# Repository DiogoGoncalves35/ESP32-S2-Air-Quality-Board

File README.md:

# ESP32-S2 Air Quality Board

An IoT Air Quality Monitor

This board is designed to measure TVOC (Total Volatile Organic Compounds), eCO2(Estimated Concentration of Carbon Dioxide) and calculate AQI (Air Quality Index) of the ambient arround. 

It's a very simple design, it was designed with the intetion of testing ENS160 + AHT21 module. 
In the end AHT21 sensor is not used because ENS160 has a heater and influences temperature readings, values are about 5 degrees higher then they shoud be.

At the moment the LVGL interface only shows eCO2 and AQI values, there is no information about TVOC, Wi-Fi and MQTT status.

------------

### Home Assistant

It supports Home Assistant via HA MQTT Auto Discovery,  there is no need to integrate this device via web interface or yaml code, it's a faster solution to integrate devices. 
The microcontroller sends TVOC, eCO2 and AQI values, and also a "On" message. Values are send every 15 seconds and if there is no value recevied 35 seconds after the last, HA assumes that the device is offline.

------------

### Schematic

The [schematic](/PCB/Schematic.pdf) is designed arround ESP32-S2 Mini Board, LCD connects via SPI and ENS160 with I²C. Board can be powered with 5V from USB connector or via ESP32-S2 Mini Board USB connector. The AJ38 module step downs the voltage to 3.3V, and powers the components. A buzzer was added but at the moment is not in use.

------------

### PCB

[This PCB](/PCB) has a very simple design, it's a 1.6 mm board with 2 copper layers, both connect to GND. Next version should have a better design, the microcontroller must be at one edge, or the GND pour needs to be removed under, it's a good practice when there is an antenna.

------------

### Code

Every line of [code](/Code/Air%20Quality%20Monitor) contains a commentary. Some libraries need a few changes.

Configuration for User_Setup.h (TFT_eSPI Library)
```arduino
#define ST7735_DRIVER

#define TFT_RGB_ORDER TFT_RGB
#define TFT_WIDTH  160
#define TFT_HEIGHT 128

#define TFT_MOSI  35
#define TFT_SCLK  36
#define TFT_CS    34  
#define TFT_DC    33  
#define TFT_RST   18
```

Configuration for lv_conf.h (lvgl Library)
```arduino
#if 1

#define LV_TICK_CUSTOM 1

#define LV_FONT_MONTSERRAT_10 1
#define LV_FONT_MONTSERRAT_12 1
#define LV_FONT_MONTSERRAT_14 1

```

------------

### Known issues

- No I²C Pull-Up (Sometimes module is not detected)
- ESP32-S2 need serial in other to work (Without module not works)
- Mounting Holes connected to GND

------------

### To-Do

- Better hardware design
- Other sensor to compare
- ESP32-S3 WROOM (No more boards)
- New LVGL interface
- Add restart button via Home Assistant
- USB-C
- Maybe LCD without the module
- Control LCD led backlight with a mosfet/transistor

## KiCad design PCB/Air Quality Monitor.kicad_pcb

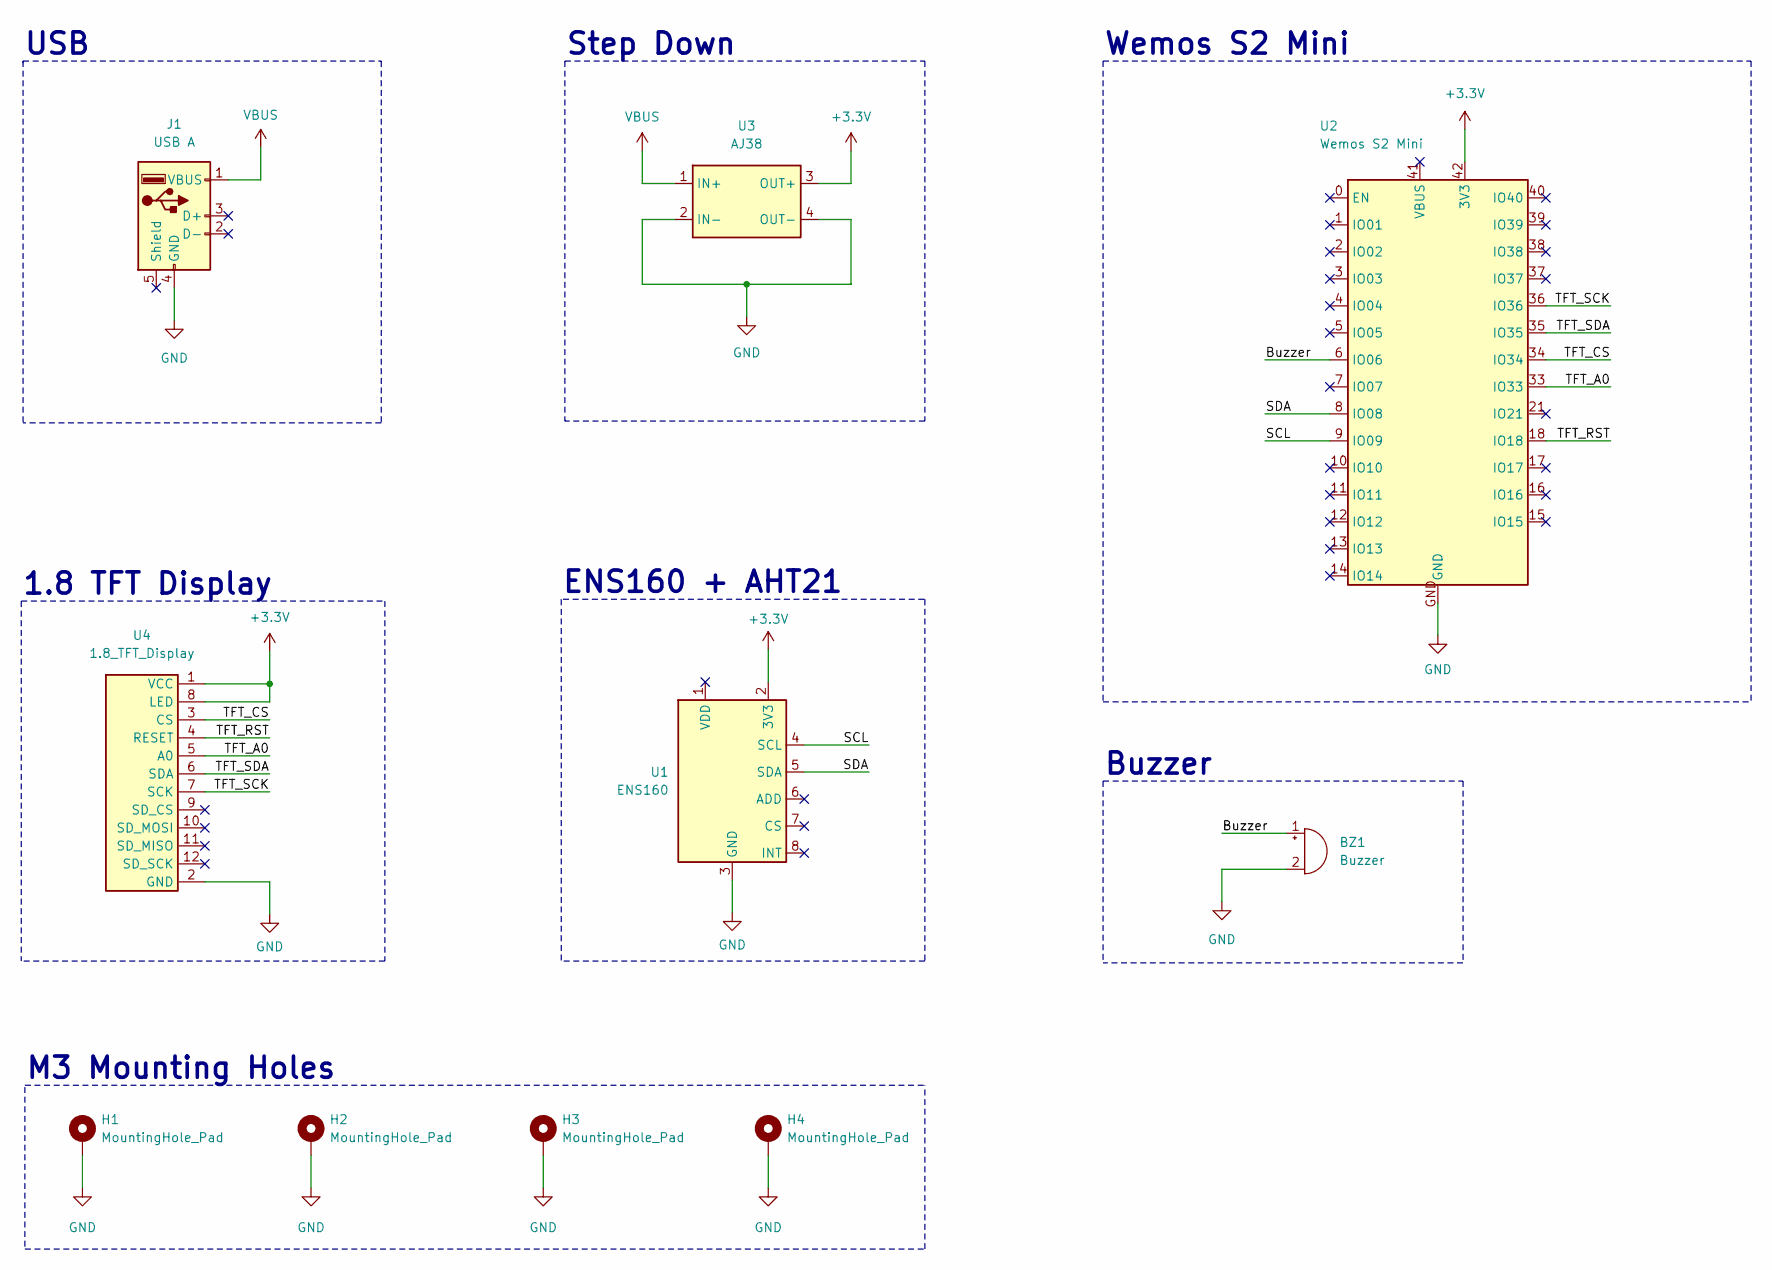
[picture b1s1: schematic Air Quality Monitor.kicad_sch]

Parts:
BZ1: Buzzer; Buzzer_12x9.5RM7.6
H1, H2, H3, H4: MountingHole_Pad; MountingHole_3.2mm_M3_Pad_Via
J1: USB A; USB_A_CONNFLY_DS1095-WNR0
U1: ENS160
U2: Wemos S2 Mini
U3: AJ38
U4: 1.8_TFT_Display; 1.8 TFT Display

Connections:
+3.3V: U1.2 (3V3), U2.42 (3V3), U3.3 (OUT+), U4.1 (VCC), U4.8 (LED)
/Buzzer: BZ1.1 (-), U2.6 (IO06)
/SCL: U1.4 (SCL), U2.9 (IO09)
/SDA: U1.5 (SDA), U2.8 (IO08)
/TFT_A0: U2.33 (IO33), U4.5 (A0)
/TFT_CS: U2.34 (IO34), U4.3 (CS)
/TFT_RST: U2.18 (IO18), U4.4 (RESET)
/TFT_SCK: U2.36 (IO36), U4.7 (SCK)
/TFT_SDA: U2.35 (IO35), U4.6 (SDA)
GND: BZ1.2 (+), H1.1, H2.1, H3.1, H4.1, J1.4 (GND), U1.3 (GND), U2.GND, U3.2 (IN-), U3.4 (OUT-), U4.2 (GND)
VBUS: J1.1 (VBUS), U3.1 (IN+)

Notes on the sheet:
Buzzer
1.8 TFT Display
Wemos S2 Mini
Step Down
ENS160 + AHT21
M3 Mounting Holes
USB

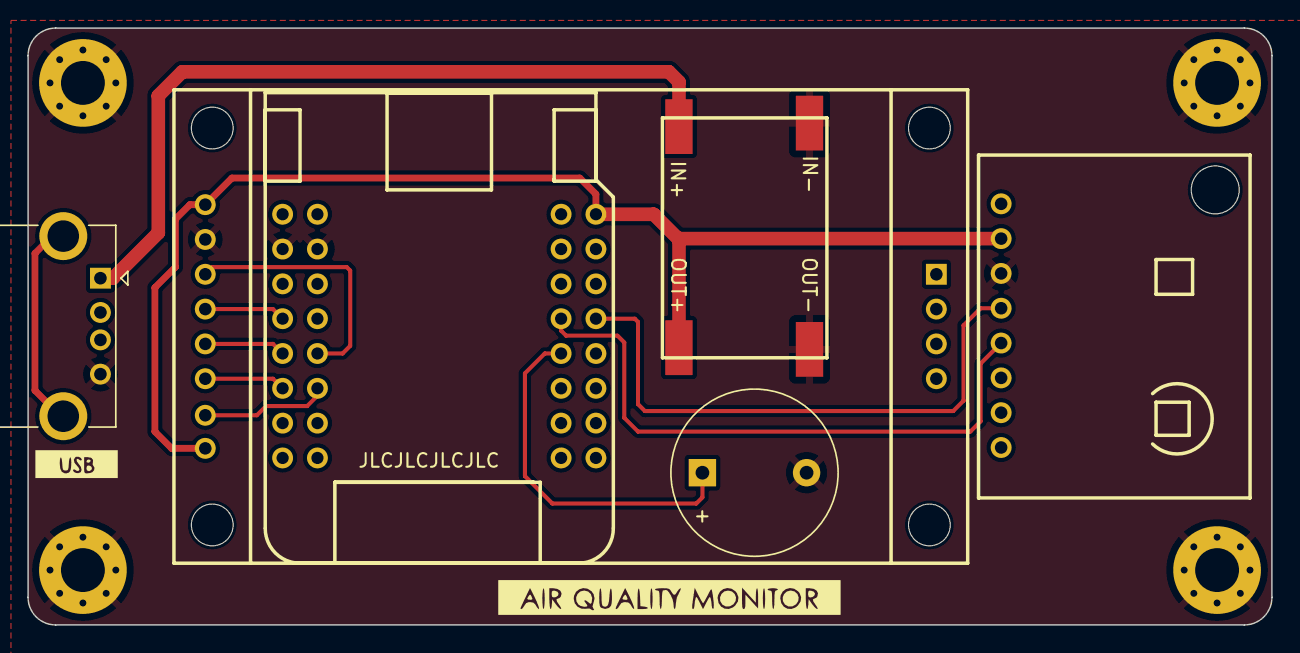
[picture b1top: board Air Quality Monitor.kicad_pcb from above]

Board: 2 copper layers, 90.8 x 43.5 mm, 10 parts (0 on the bottom side), 11 nets.

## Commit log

2024-01-07 Publish
